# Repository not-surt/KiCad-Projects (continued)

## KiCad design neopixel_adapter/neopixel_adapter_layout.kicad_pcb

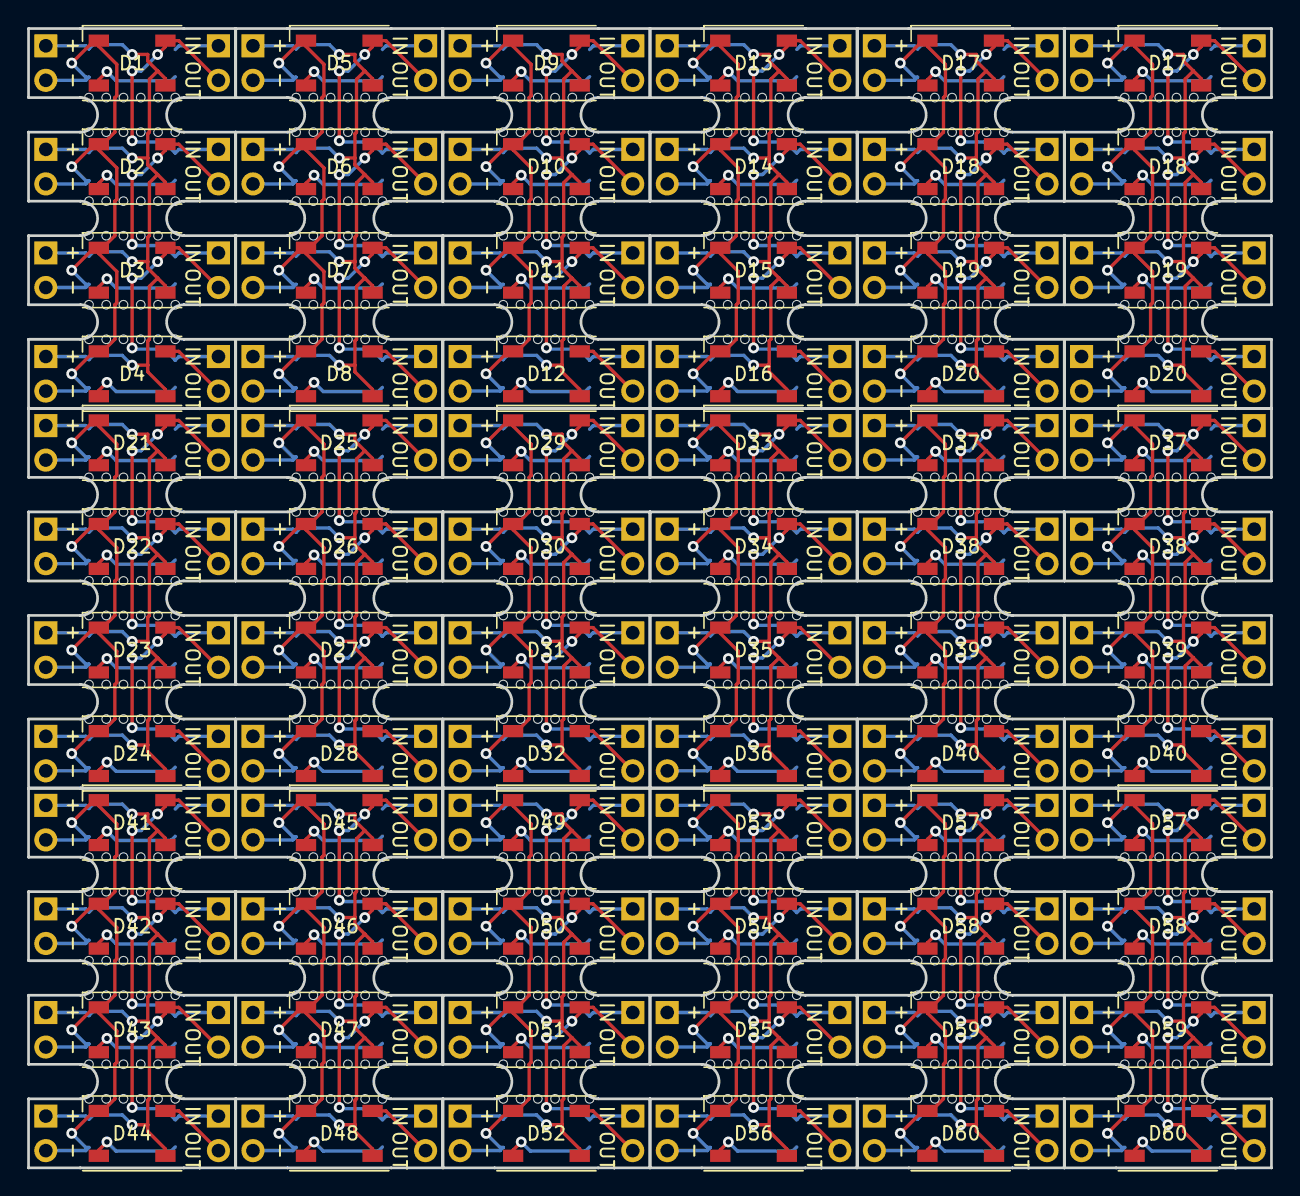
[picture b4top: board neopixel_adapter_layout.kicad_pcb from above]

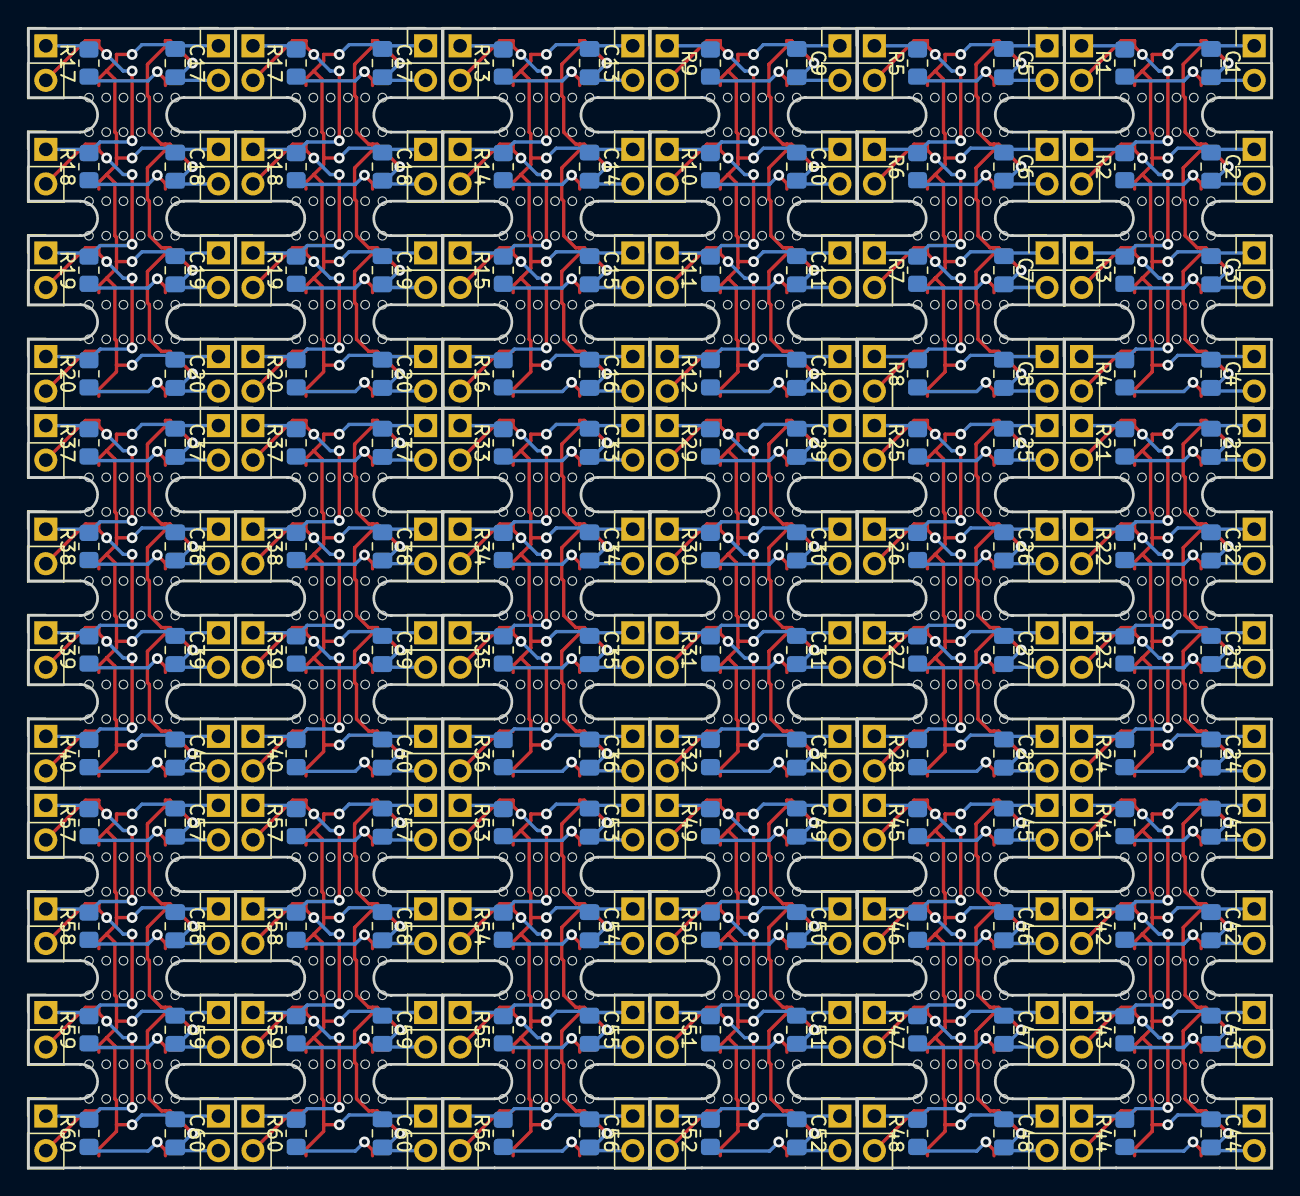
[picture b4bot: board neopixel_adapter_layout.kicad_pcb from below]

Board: 2 copper layers, 91.4 x 83.8 mm, 360 parts (288 on the bottom side), 11 nets.

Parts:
C1, C2, C3, C4, C5, C6, C7, C8, C9, C10, C11, C12, C13, C14, C15, C16, C17, C17#2, C18, C18#2, C19, C19#2, C20, C20#2, C21, C22, C23, C24, C25, C26, C27, C28, C29, C30, C31, C32, C33, C34, C35, C36, C37, C37#2, C38, C38#2, C39, C39#2, C40, C40#2, C41, C42, C43, C44, C45, C46, C47, C48, C49, C50, C51, C52, C53, C54, C55, C56, C57, C57#2, C58, C58#2, C59, C59#2, C60, C60#2: 0.1uF; C_0805_2012Metric_Pad1.18x1.45mm_HandSolder
D1, D2, D3, D4, D5, D6, D7, D8, D9, D10, D11, D12, D13, D14, D15, D16, D17, D17#2, D18, D18#2, D19, D19#2, D20, D20#2, D21, D22, D23, D24, D25, D26, D27, D28, D29, D30, D31, D32, D33, D34, D35, D36, D37, D37#2, D38, D38#2, D39, D39#2, D40, D40#2, D41, D42, D43, D44, D45, D46, D47, D48, D49, D50, D51, D52, D53, D54, D55, D56, D57, D57#2, D58, D58#2, D59, D59#2, D60, D60#2: WS2812B; LED_WS2812B_PLCC4_5.0x5.0mm_P3.2mm
J1, J2, J3, J4, J5, J6, J7, J8, J9, J10, J11, J12, J13, J14, J15, J16, J17, J18, J19, J20, J21, J22, J23, J24, J25, J26, J27, J28, J29, J30, J31, J32, J33, J33#2, J34, J34#2, J35, J35#2, J36, J36#2, J37, J37#2, J38, J38#2, J39, J39#2, J40, J40#2, J41, J42, J43, J44, J45, J46, J47, J48, J49, J50, J51, J52, J53, J54, J55, J56, J57, J58, J59, J60, J61, J62, J63, J64, J65, J66, J67, J68, J69, J70, J71, J72, J73, J73#2, J74, J74#2, J75, J75#2, J76, J76#2, J77, J77#2, J78, J78#2, J79, J79#2, J80, J80#2, J81, J82, J83, J84, J85, J86, J87, J88, J89, J90, J91, J92, J93, J94, J95, J96, J97, J98, J99, J100, J101, J102, J103, J104, J105, J106, J107, J108, J109, J110, J111, J112, J113, J113#2, J114, J114#2, J115, J115#2, J116, J116#2, J117, J117#2, J118, J118#2, J119, J119#2, J120, J120#2: Conn_01x02; PinHeader_1x02_P2.54mm_Vertical
R1, R2, R3, R4, R5, R6, R7, R8, R9, R10, R11, R12, R13, R14, R15, R16, R17, R17#2, R18, R18#2, R19, R19#2, R20, R20#2, R21, R22, R23, R24, R25, R26, R27, R28, R29, R30, R31, R32, R33, R34, R35, R36, R37, R37#2, R38, R38#2, R39, R39#2, R40, R40#2, R41, R42, R43, R44, R45, R46, R47, R48, R49, R50, R51, R52, R53, R54, R55, R56, R57, R57#2, R58, R58#2, R59, R59#2, R60, R60#2: 470R; R_0805_2012Metric_Pad1.20x1.40mm_HandSolder

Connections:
/NeoPixel Module 1/DIN: J2.1, J10.1, J18.1, J26.1, J34.1, J34#2.1, J42.1, J50.1, J58.1, J66.1, J74.1, J74#2.1, J82.1, J90.1, J98.1, J106.1, J114.1, J114#2.1, R1.1, R5.1, R9.1, R13.1, R17.1, R17#2.1, R21.1, R25.1, R29.1, R33.1, R37.1, R37#2.1, R41.1, R45.1, R49.1, R53.1, R57.1, R57#2.1
/NeoPixel Module 1/DOUT: D1.2 (DOUT), D5.2 (DOUT), D9.2 (DOUT), D13.2 (DOUT), D17.2 (DOUT), D17#2.2 (DOUT), D21.2 (DOUT), D25.2 (DOUT), D29.2 (DOUT), D33.2 (DOUT), D37.2 (DOUT), D37#2.2 (DOUT), D41.2 (DOUT), D45.2 (DOUT), D49.2 (DOUT), D53.2 (DOUT), D57.2 (DOUT), D57#2.2 (DOUT), J2.2, J4.1, J10.2, J12.1, J18.2, J20.1, J26.2, J28.1, J34.2, J34#2.2, J36.1, J36#2.1, J42.2, J44.1, J50.2, J52.1, J58.2, J60.1, J66.2, J68.1, J74.2, J74#2.2, J76.1, J76#2.1, J82.2, J84.1, J90.2, J92.1, J98.2, J100.1, J106.2, J108.1, J114.2, J114#2.2, J116.1, J116#2.1, R2.1, R6.1, R10.1, R14.1, R18.1, R18#2.1, R22.1, R26.1, R30.1, R34.1, R38.1, R38#2.1, R42.1, R46.1, R50.1, R54.1, R58.1, R58#2.1
/NeoPixel Module 1/VDD: C1.2, C2.2, C3.2, C4.2, C5.2, C6.2, C7.2, C8.2, C9.2, C10.2, C11.2, C12.2, C13.2, C14.2, C15.2, C16.2, C17.2, C17#2.2, C18.2, C18#2.2, C19.2, C19#2.2, C20.2, C20#2.2, C21.2, C22.2, C23.2, C24.2, C25.2, C26.2, C27.2, C28.2, C29.2, C30.2, C31.2, C32.2, C33.2, C34.2, C35.2, C36.2, C37.2, C37#2.2, C38.2, C38#2.2, C39.2, C39#2.2, C40.2, C40#2.2, C41.2, C42.2, C43.2, C44.2, C45.2, C46.2, C47.2, C48.2, C49.2, C50.2, C51.2, C52.2, C53.2, C54.2, C55.2, C56.2, C57.2, C57#2.2, C58.2, C58#2.2, C59.2, C59#2.2, C60.2, C60#2.2, D1.1 (VDD), D2.1 (VDD), D3.1 (VDD), D4.1 (VDD), D5.1 (VDD), D6.1 (VDD), D7.1 (VDD), D8.1 (VDD), D9.1 (VDD), D10.1 (VDD), D11.1 (VDD), D12.1 (VDD), D13.1 (VDD), D14.1 (VDD), D15.1 (VDD), D16.1 (VDD), D17.1 (VDD), D17#2.1 (VDD), D18.1 (VDD), D18#2.1 (VDD), D19.1 (VDD), D19#2.1 (VDD), D20.1 (VDD), D20#2.1 (VDD), D21.1 (VDD), D22.1 (VDD), D23.1 (VDD), D24.1 (VDD), D25.1 (VDD), D26.1 (VDD), D27.1 (VDD), D28.1 (VDD), D29.1 (VDD), D30.1 (VDD), D31.1 (VDD), D32.1 (VDD), D33.1 (VDD), D34.1 (VDD), D35.1 (VDD), D36.1 (VDD), D37.1 (VDD), D37#2.1 (VDD), D38.1 (VDD), D38#2.1 (VDD), D39.1 (VDD), D39#2.1 (VDD), D40.1 (VDD), D40#2.1 (VDD), D41.1 (VDD), D42.1 (VDD), D43.1 (VDD), D44.1 (VDD), D45.1 (VDD), D46.1 (VDD), D47.1 (VDD), D48.1 (VDD), D49.1 (VDD), D50.1 (VDD), D51.1 (VDD), D52.1 (VDD), D53.1 (VDD), D54.1 (VDD), D55.1 (VDD), D56.1 (VDD), D57.1 (VDD), D57#2.1 (VDD), D58.1 (VDD), D58#2.1 (VDD), D59.1 (VDD), D59#2.1 (VDD), D60.1 (VDD), D60#2.1 (VDD), J1.1, J3.1, J5.1, J7.1, J9.1, J11.1, J13.1, J15.1, J17.1, J19.1, J21.1, J23.1, J25.1, J27.1, J29.1, J31.1, J33.1, J33#2.1, J35.1, J35#2.1, J37.1, J37#2.1, J39.1, J39#2.1, J41.1, J43.1, J45.1, J47.1, J49.1, J51.1, J53.1, J55.1, J57.1, J59.1, J61.1, J63.1, J65.1, J67.1, J69.1, J71.1, J73.1, J73#2.1, J75.1, J75#2.1, J77.1, J77#2.1, J79.1, J79#2.1, J81.1, J83.1, J85.1, J87.1, J89.1, J91.1, J93.1, J95.1, J97.1, J99.1, J101.1, J103.1, J105.1, J107.1, J109.1, J111.1, J113.1, J113#2.1, J115.1, J115#2.1, J117.1, J117#2.1, J119.1, J119#2.1
/NeoPixel Module 1/VSS: C1.1, C2.1, C3.1, C4.1, C5.1, C6.1, C7.1, C8.1, C9.1, C10.1, C11.1, C12.1, C13.1, C14.1, C15.1, C16.1, C17.1, C17#2.1, C18.1, C18#2.1, C19.1, C19#2.1, C20.1, C20#2.1, C21.1, C22.1, C23.1, C24.1, C25.1, C26.1, C27.1, C28.1, C29.1, C30.1, C31.1, C32.1, C33.1, C34.1, C35.1, C36.1, C37.1, C37#2.1, C38.1, C38#2.1, C39.1, C39#2.1, C40.1, C40#2.1, C41.1, C42.1, C43.1, C44.1, C45.1, C46.1, C47.1, C48.1, C49.1, C50.1, C51.1, C52.1, C53.1, C54.1, C55.1, C56.1, C57.1, C57#2.1, C58.1, C58#2.1, C59.1, C59#2.1, C60.1, C60#2.1, D1.3 (VSS), D2.3 (VSS), D3.3 (VSS), D4.3 (VSS), D5.3 (VSS), D6.3 (VSS), D7.3 (VSS), D8.3 (VSS), D9.3 (VSS), D10.3 (VSS), D11.3 (VSS), D12.3 (VSS), D13.3 (VSS), D14.3 (VSS), D15.3 (VSS), D16.3 (VSS), D17.3 (VSS), D17#2.3 (VSS), D18.3 (VSS), D18#2.3 (VSS), D19.3 (VSS), D19#2.3 (VSS), D20.3 (VSS), D20#2.3 (VSS), D21.3 (VSS), D22.3 (VSS), D23.3 (VSS), D24.3 (VSS), D25.3 (VSS), D26.3 (VSS), D27.3 (VSS), D28.3 (VSS), D29.3 (VSS), D30.3 (VSS), D31.3 (VSS), D32.3 (VSS), D33.3 (VSS), D34.3 (VSS), D35.3 (VSS), D36.3 (VSS), D37.3 (VSS), D37#2.3 (VSS), D38.3 (VSS), D38#2.3 (VSS), D39.3 (VSS), D39#2.3 (VSS), D40.3 (VSS), D40#2.3 (VSS), D41.3 (VSS), D42.3 (VSS), D43.3 (VSS), D44.3 (VSS), D45.3 (VSS), D46.3 (VSS), D47.3 (VSS), D48.3 (VSS), D49.3 (VSS), D50.3 (VSS), D51.3 (VSS), D52.3 (VSS), D53.3 (VSS), D54.3 (VSS), D55.3 (VSS), D56.3 (VSS), D57.3 (VSS), D57#2.3 (VSS), D58.3 (VSS), D58#2.3 (VSS), D59.3 (VSS), D59#2.3 (VSS), D60.3 (VSS), D60#2.3 (VSS), J1.2, J3.2, J5.2, J7.2, J9.2, J11.2, J13.2, J15.2, J17.2, J19.2, J21.2, J23.2, J25.2, J27.2, J29.2, J31.2, J33.2, J33#2.2, J35.2, J35#2.2, J37.2, J37#2.2, J39.2, J39#2.2, J41.2, J43.2, J45.2, J47.2, J49.2, J51.2, J53.2, J55.2, J57.2, J59.2, J61.2, J63.2, J65.2, J67.2, J69.2, J71.2, J73.2, J73#2.2, J75.2, J75#2.2, J77.2, J77#2.2, J79.2, J79#2.2, J81.2, J83.2, J85.2, J87.2, J89.2, J91.2, J93.2, J95.2, J97.2, J99.2, J101.2, J103.2, J105.2, J107.2, J109.2, J111.2, J113.2, J113#2.2, J115.2, J115#2.2, J117.2, J117#2.2, J119.2, J119#2.2
/NeoPixel Module 2/DOUT: D2.2 (DOUT), D6.2 (DOUT), D10.2 (DOUT), D14.2 (DOUT), D18.2 (DOUT), D18#2.2 (DOUT), D22.2 (DOUT), D26.2 (DOUT), D30.2 (DOUT), D34.2 (DOUT), D38.2 (DOUT), D38#2.2 (DOUT), D42.2 (DOUT), D46.2 (DOUT), D50.2 (DOUT), D54.2 (DOUT), D58.2 (DOUT), D58#2.2 (DOUT), J4.2, J6.1, J12.2, J14.1, J20.2, J22.1, J28.2, J30.1, J36.2, J36#2.2, J38.1, J38#2.1, J44.2, J46.1, J52.2, J54.1, J60.2, J62.1, J68.2, J70.1, J76.2, J76#2.2, J78.1, J78#2.1, J84.2, J86.1, J92.2, J94.1, J100.2, J102.1, J108.2, J110.1, J116.2, J116#2.2, J118.1, J118#2.1, R3.1, R7.1, R11.1, R15.1, R19.1, R19#2.1, R23.1, R27.1, R31.1, R35.1, R39.1, R39#2.1, R43.1, R47.1, R51.1, R55.1, R59.1, R59#2.1
/NeoPixel Module 3/DOUT: D3.2 (DOUT), D7.2 (DOUT), D11.2 (DOUT), D15.2 (DOUT), D19.2 (DOUT), D19#2.2 (DOUT), D23.2 (DOUT), D27.2 (DOUT), D31.2 (DOUT), D35.2 (DOUT), D39.2 (DOUT), D39#2.2 (DOUT), D43.2 (DOUT), D47.2 (DOUT), D51.2 (DOUT), D55.2 (DOUT), D59.2 (DOUT), D59#2.2 (DOUT), J6.2, J8.1, J14.2, J16.1, J22.2, J24.1, J30.2, J32.1, J38.2, J38#2.2, J40.1, J40#2.1, J46.2, J48.1, J54.2, J56.1, J62.2, J64.1, J70.2, J72.1, J78.2, J78#2.2, J80.1, J80#2.1, J86.2, J88.1, J94.2, J96.1, J102.2, J104.1, J110.2, J112.1, J118.2, J118#2.2, J120.1, J120#2.1, R4.1, R8.1, R12.1, R16.1, R20.1, R20#2.1, R24.1, R28.1, R32.1, R36.1, R40.1, R40#2.1, R44.1, R48.1, R52.1, R56.1, R60.1, R60#2.1
/NeoPixel Module 4/DOUT: D4.2 (DOUT), D8.2 (DOUT), D12.2 (DOUT), D16.2 (DOUT), D20.2 (DOUT), D20#2.2 (DOUT), D24.2 (DOUT), D28.2 (DOUT), D32.2 (DOUT), D36.2 (DOUT), D40.2 (DOUT), D40#2.2 (DOUT), D44.2 (DOUT), D48.2 (DOUT), D52.2 (DOUT), D56.2 (DOUT), D60.2 (DOUT), D60#2.2 (DOUT), J8.2, J16.2, J24.2, J32.2, J40.2, J40#2.2, J48.2, J56.2, J64.2, J72.2, J80.2, J80#2.2, J88.2, J96.2, J104.2, J112.2, J120.2, J120#2.2
unnamed: D1.4 (DIN), D5.4 (DIN), D9.4 (DIN), D13.4 (DIN), D17.4 (DIN), D17#2.4 (DIN), D21.4 (DIN), D25.4 (DIN), D29.4 (DIN), D33.4 (DIN), D37.4 (DIN), D37#2.4 (DIN), D41.4 (DIN), D45.4 (DIN), D49.4 (DIN), D53.4 (DIN), D57.4 (DIN), D57#2.4 (DIN), R1.2, R5.2, R9.2, R13.2, R17.2, R17#2.2, R21.2, R25.2, R29.2, R33.2, R37.2, R37#2.2, R41.2, R45.2, R49.2, R53.2, R57.2, R57#2.2
unnamed: D2.4 (DIN), D6.4 (DIN), D10.4 (DIN), D14.4 (DIN), D18.4 (DIN), D18#2.4 (DIN), D22.4 (DIN), D26.4 (DIN), D30.4 (DIN), D34.4 (DIN), D38.4 (DIN), D38#2.4 (DIN), D42.4 (DIN), D46.4 (DIN), D50.4 (DIN), D54.4 (DIN), D58.4 (DIN), D58#2.4 (DIN), R2.2, R6.2, R10.2, R14.2, R18.2, R18#2.2, R22.2, R26.2, R30.2, R34.2, R38.2, R38#2.2, R42.2, R46.2, R50.2, R54.2, R58.2, R58#2.2
unnamed: D3.4 (DIN), D7.4 (DIN), D11.4 (DIN), D15.4 (DIN), D19.4 (DIN), D19#2.4 (DIN), D23.4 (DIN), D27.4 (DIN), D31.4 (DIN), D35.4 (DIN), D39.4 (DIN), D39#2.4 (DIN), D43.4 (DIN), D47.4 (DIN), D51.4 (DIN), D55.4 (DIN), D59.4 (DIN), D59#2.4 (DIN), R3.2, R7.2, R11.2, R15.2, R19.2, R19#2.2, R23.2, R27.2, R31.2, R35.2, R39.2, R39#2.2, R43.2, R47.2, R51.2, R55.2, R59.2, R59#2.2
unnamed: D4.4 (DIN), D8.4 (DIN), D12.4 (DIN), D16.4 (DIN), D20.4 (DIN), D20#2.4 (DIN), D24.4 (DIN), D28.4 (DIN), D32.4 (DIN), D36.4 (DIN), D40.4 (DIN), D40#2.4 (DIN), D44.4 (DIN), D48.4 (DIN), D52.4 (DIN), D56.4 (DIN), D60.4 (DIN), D60#2.4 (DIN), R4.2, R8.2, R12.2, R16.2, R20.2, R20#2.2, R24.2, R28.2, R32.2, R36.2, R40.2, R40#2.2, R44.2, R48.2, R52.2, R56.2, R60.2, R60#2.2

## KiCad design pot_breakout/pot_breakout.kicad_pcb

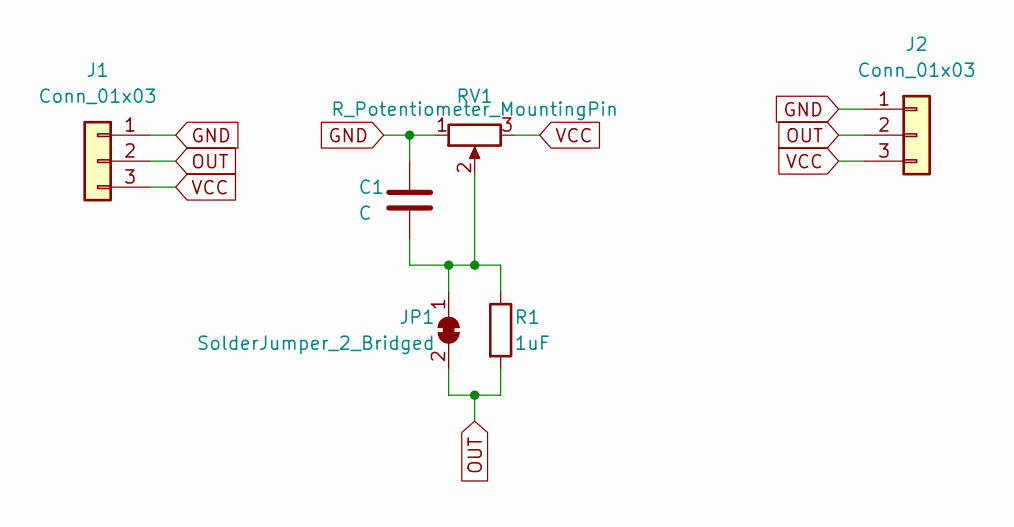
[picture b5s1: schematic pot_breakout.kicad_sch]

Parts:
C1: C; C_0805_2012Metric_Pad1.18x1.45mm_HandSolder
J1, J2: Conn_01x03; PinHeader_1x03_P2.54mm_Vertical_no_silk
JP1: SolderJumper_2_Bridged; SolderJumper-2_P1.3mm_Bridged_RoundedPad1.0x1.5mm
R1: 1uF; R_0805_2012Metric_Pad1.20x1.40mm_HandSolder
RV1: R_Potentiometer_MountingPin; Potentiometer_Alpha_RD901F-40-00D_Single_Vertical

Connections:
GND: C1.1, J1.1, J2.1, RV1.1
unnamed: C1.2, JP1.1 (A), R1.1, RV1.2
OUT: J1.2, J2.2, JP1.2 (B), R1.2
VCC: J1.3, J2.3, RV1.3

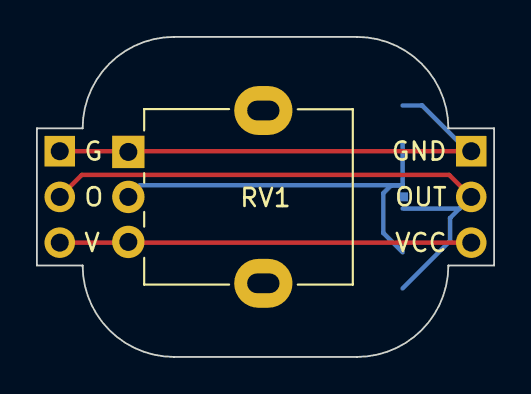
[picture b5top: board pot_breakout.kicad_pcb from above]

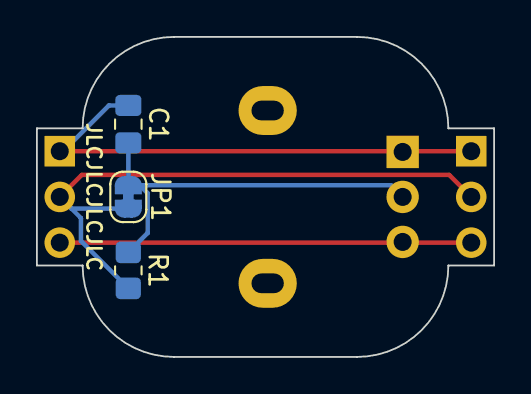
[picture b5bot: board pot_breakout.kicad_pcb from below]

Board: 2 copper layers, 25.4 x 17.8 mm, 6 parts (3 on the bottom side), 4 nets.
